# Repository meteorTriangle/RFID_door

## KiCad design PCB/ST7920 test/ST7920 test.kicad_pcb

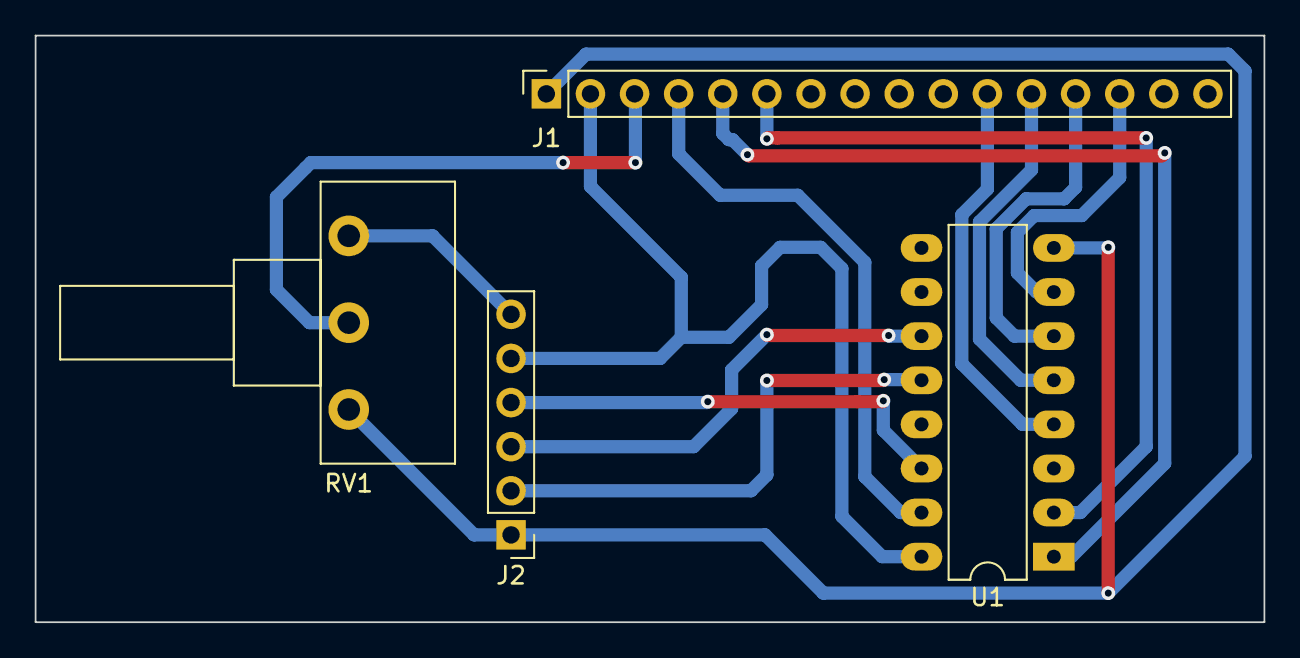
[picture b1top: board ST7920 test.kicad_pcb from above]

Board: 2 copper layers, 70.8 x 33.8 mm, 4 parts (0 on the bottom side), 14 nets.

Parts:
J1: Conn_01x16; PinSocket_1x16_P2.54mm_Vertical
J2: Conn_01x06; PinHeader_1x06_P2.54mm_Vertical
RV1: R_Potentiometer_US; Potentiometer_Piher_T-16H_Single_Horizontal
U1: 74HC595; DIP-16_W7.62mm_LongPads

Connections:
/3.3V: J1.2, J2.5, U1.16 (VCC)
/5V: J2.6, RV1.1
/DB4: J1.11, U1.4 (QE)
/DB5: J1.12, U1.5 (QF)
/DB6: J1.13, U1.6 (QG)
/DB7: J1.14, U1.7 (QH)
/Data in: J2.4, U1.14 (SER)
/Enable: J1.6, U1.2 (QC)
/GND: J1.1, J2.1, RV1.3, U1.8 (GND)
/RS: J1.4, U1.15 (QA)
/R/W: J1.5, U1.1 (QB)
/SR clk: J2.3, U1.11 (SRCLK)
/Vref: J1.3, RV1.2
/latch: J2.2, U1.12 (RCLK)

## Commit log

2022-08-16 first
2022-08-16 V1.0.2
2022-08-16 V1.0.3
2023-04-19 Create LICENSE
2023-06-20 front 3d model
2023-06-20 spi init 1-1
2023-06-21 rc522 init test
